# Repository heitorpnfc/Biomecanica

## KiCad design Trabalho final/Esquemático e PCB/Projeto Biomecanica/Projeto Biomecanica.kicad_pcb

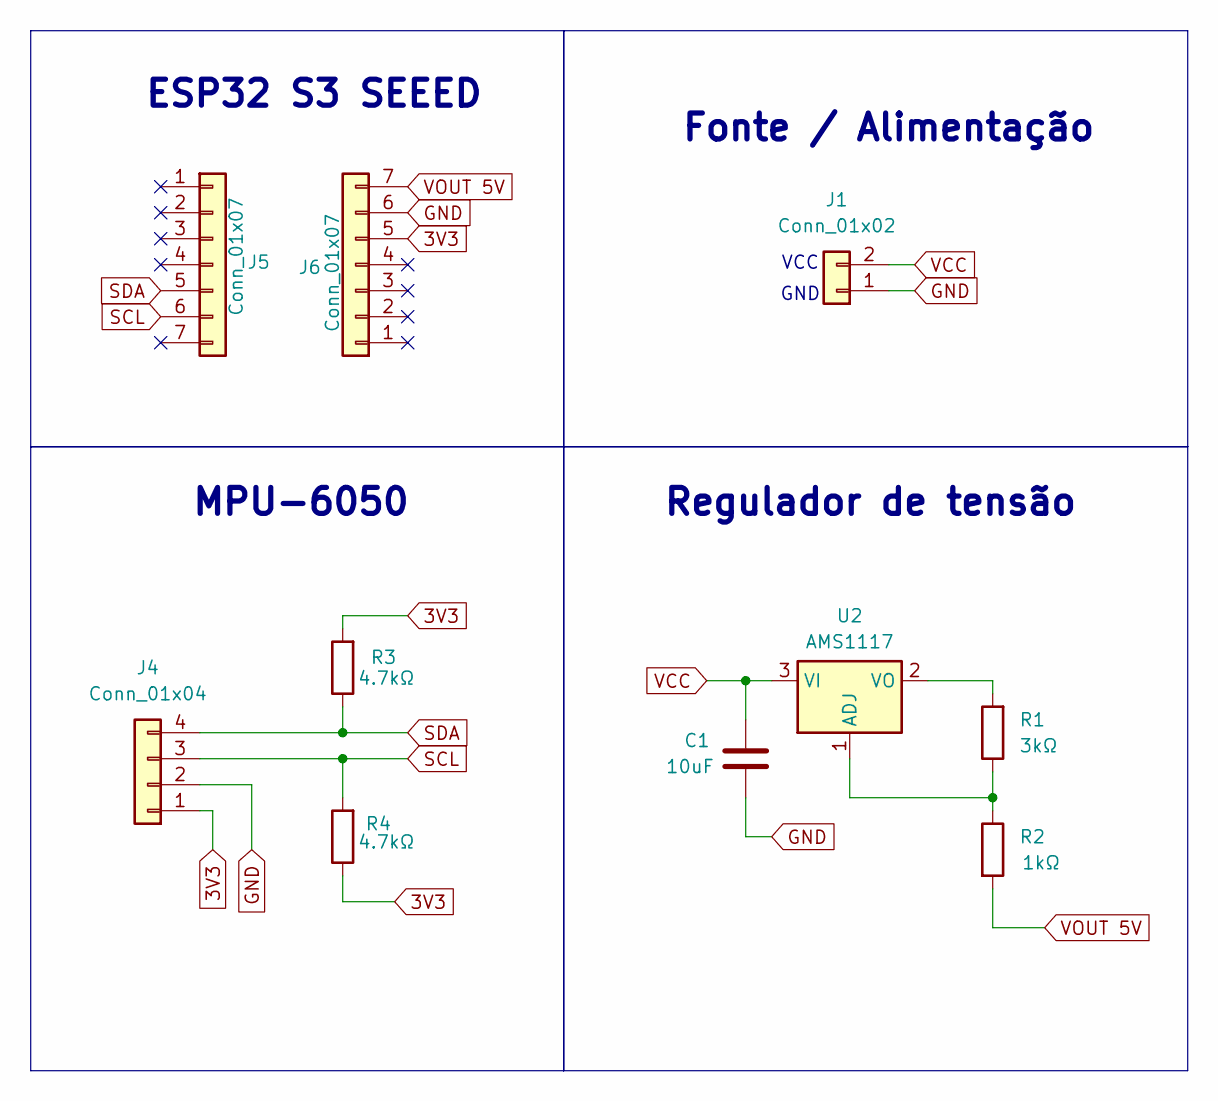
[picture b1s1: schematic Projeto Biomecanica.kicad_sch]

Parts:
C1: 10uF; CP_Radial_D4.0mm_P1.50mm
J1: Conn_01x02; PinSocket_1x02_P2.54mm_Vertical
J4: Conn_01x04; PinSocket_1x04_P2.54mm_Vertical
J5, J6: Conn_01x07; PinSocket_1x07_P2.54mm_Vertical
R1: 3kΩ; R_Axial_DIN0204_L3.6mm_D1.6mm_P5.08mm_Horizontal
R2: 1kΩ; R_Axial_DIN0204_L3.6mm_D1.6mm_P5.08mm_Horizontal
R3, R4: 4.7kΩ; R_Axial_DIN0204_L3.6mm_D1.6mm_P5.08mm_Horizontal
U2: AMS1117; SOT-223-3_TabPin2

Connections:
3V3: J4.1, J6.5, R3.2, R4.1
GND: C1.2, J1.1, J4.2, J6.6
unnamed: R1.1, R2.1, U2.1 (ADJ)
unnamed: R1.2, U2.2 (VO)
SCL: J4.3, J5.6, R4.2
SDA: J4.4, J5.5, R3.1
VCC: C1.1, J1.2, U2.3 (VI)
VOUT 5V: J6.7, R2.2

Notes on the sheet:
Regulador de tensão
Fonte / Alimentação
VCC
MPU-6050
GND
ESP32 S3 SEEED

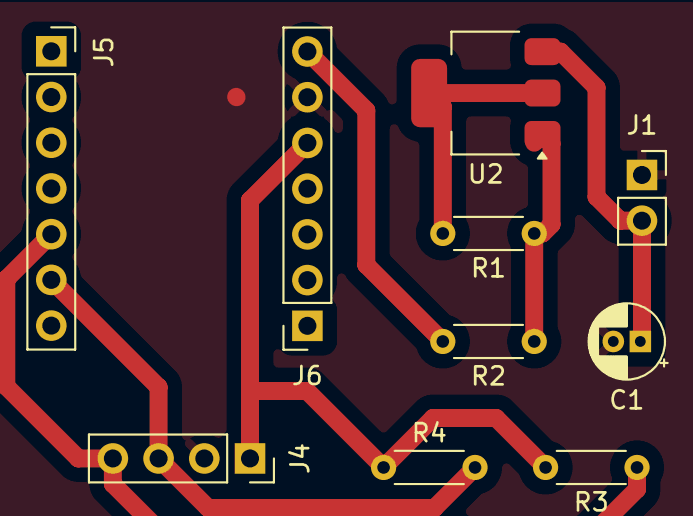
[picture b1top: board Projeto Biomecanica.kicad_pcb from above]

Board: 2 copper layers, 10 parts (0 on the bottom side), 8 nets.

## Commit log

2025-03-31 inicio app
2025-04-01 Conversando melhor com o banco de dados
2025-04-07 atividade salto vertical
2025-04-07 atualização dados
2025-04-10 tarefa 7
2025-04-21 sensor 1 funcional
2025-04-21 Implementação do código
2025-04-24 esq + pcb update
2025-04-24 Caixa
